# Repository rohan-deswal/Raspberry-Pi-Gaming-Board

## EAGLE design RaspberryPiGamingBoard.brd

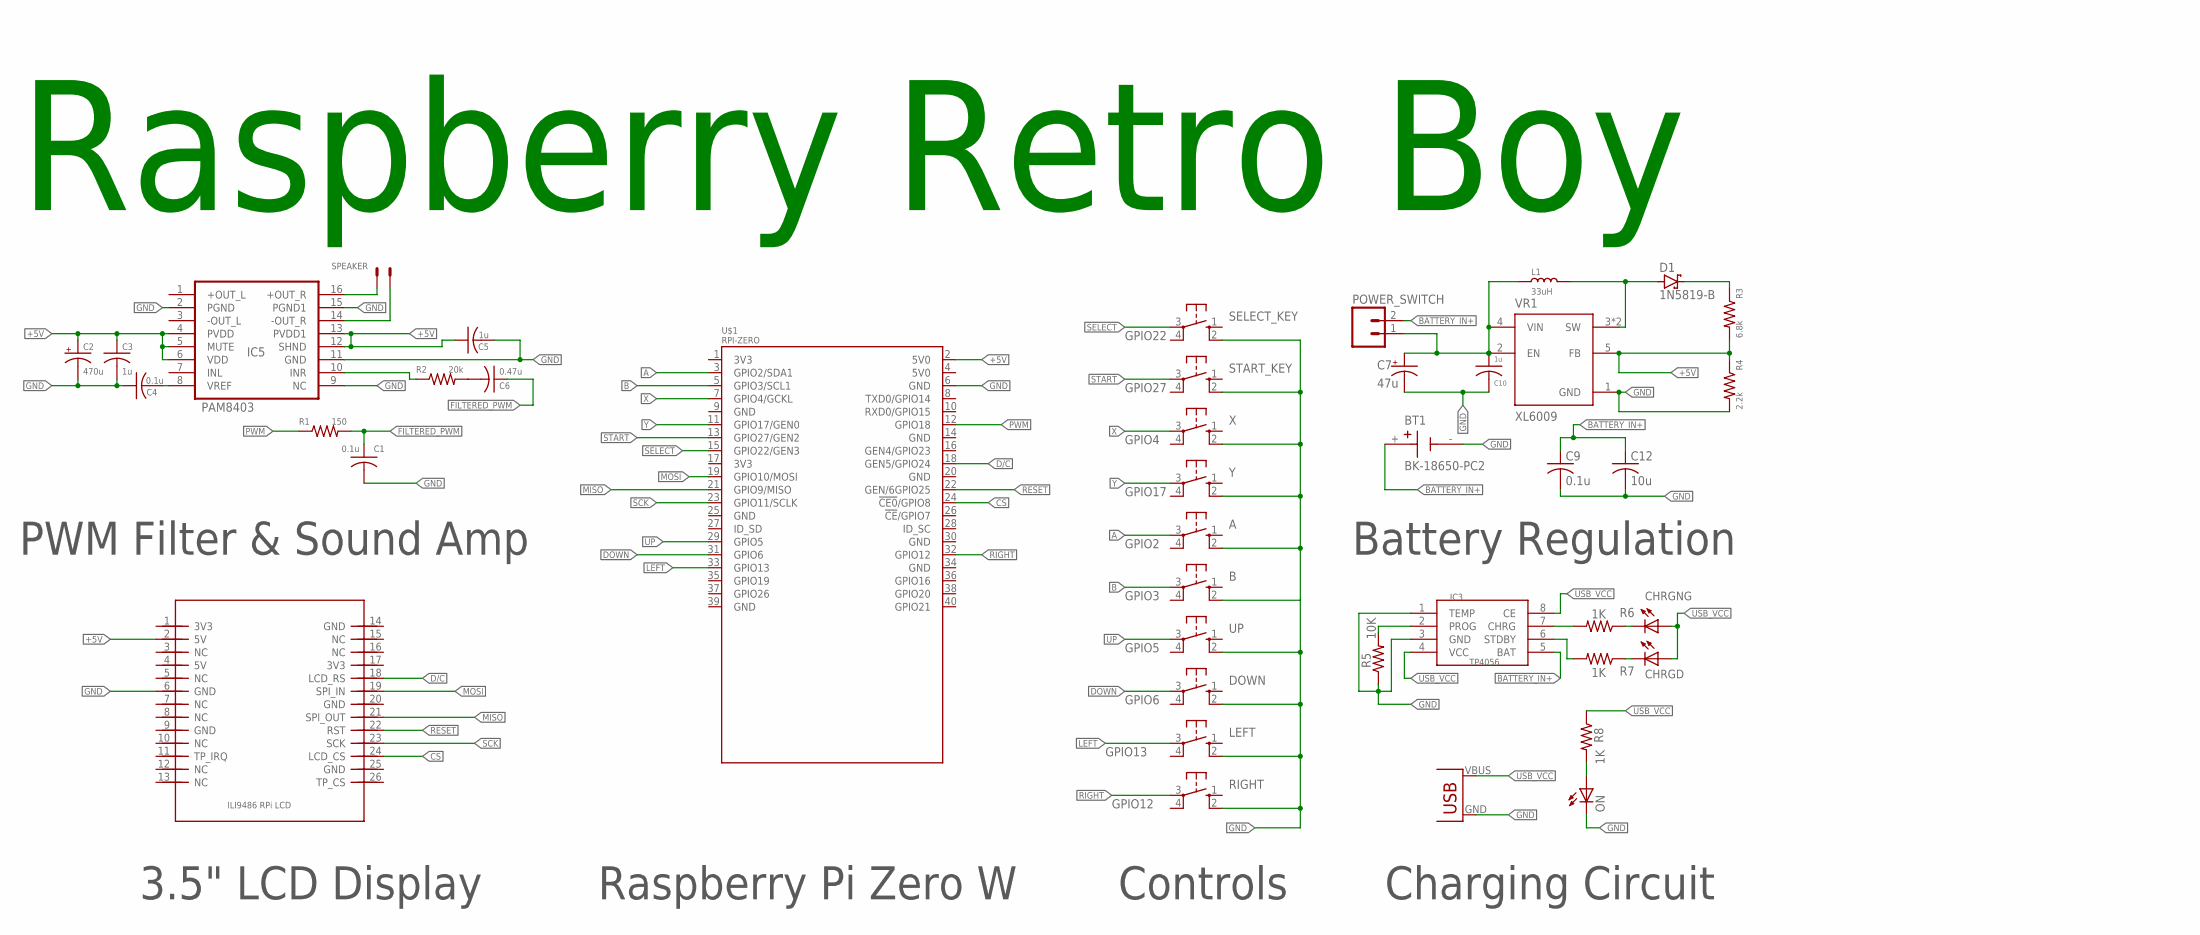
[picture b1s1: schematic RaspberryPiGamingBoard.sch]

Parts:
A: 40-XX; B3F-40XX
B: 40-XX; B3F-40XX
BT1: BK-18650-PC2; BAT_BK-18650-PC2
C1: 0.1u; C0603
C2: 470u; E5-10,5
C3, C5, C10: 1u; C0805
C4, C9: 0.1u; C0805
C6: 0.47u; C0603
C7: 47u; E5-8,5
C12: 10u; C0805
CHRGD: LED3MM
CHRGNG: LED3MM
D1: 1N5819-B; DO41-7.6
DOWN: 40-XX; B3F-40XX
IC3: TP4056; SOP-8
IC5: PAM8403; SOP-16
L1: 33uH; INDUCTOR_INT2-3.5-D6.5XH8.0MM
LEFT: 40-XX; B3F-40XX
ON: LED3MM
POWER_SWITCH: M02; 02P
R1: 150; 0207/10
R2: 20k; 0207/10
R3: 6.8k; 0207/10
R4: 2.2k; 0207/10
R5: 10K; 0207/7
R6, R7, R8: 1K; 0207/7
RIGHT: 40-XX; B3F-40XX
SELECT_KEY: 40-XX; B3F-40XX
SPEAKER: SPEAKER; JST-XH-02-PACKAGE-LONG-PAD
START_KEY: 40-XX; B3F-40XX
U$1: RPI-ZERO; RASP_PI_ZERO_BOARD_FULL
U$2: 3.5INCHRPIDISPLAY; 3.5INCH_RPI_LCD
U$3: USB(POWER)
UP: 40-XX; B3F-40XX
VR1: XL6009; DPAK170P1435X465-6N
X: 40-XX; B3F-40XX
Y: 40-XX; B3F-40XX

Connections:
+5V: C2.+, C3.1, C5.1, IC5.4 (PVDD), IC5.5 (MUTE), IC5.6 (VDD), IC5.12 (SHND), IC5.13 (PVDD1), R3.2, R4.1, U$1.2 (5V0), U$2.2 (5V), VR1.5 (FB)
BATTERY_IN+: BT1.+, C9.1, C12.1, IC3.5 (BAT), POWER_SWITCH.2
FILTERED_PWM: C1.1, C6.1, R1.2
GND: A.2 (S1), B.2 (S1), BT1.-, C1.2, C2.-, C3.2, C4.1, C5.2, C7.-, C9.2, C10.2, C12.2, DOWN.2 (S1), IC3.1 (TEMP), IC3.3 (GND), IC5.2 (PGND), IC5.9 (NC), IC5.11 (GND), IC5.15 (PGND1), LEFT.2 (S1), ON.K (C), R4.2, R5.1, RIGHT.2 (S1), SELECT_KEY.2 (S1), START_KEY.2 (S1), U$1.6 (GND), U$2.6 (GND), U$3.GND, UP.2 (S1), VR1.1 (GND), X.2 (S1), Y.2 (S1)
GPIO2: A.3, U$1.3 (GPIO2/SDA1)
GPIO3: B.3, U$1.5 (GPIO3/SCL1)
GPIO4: U$1.7 (GPIO4/GCKL), X.3
GPIO5: U$1.29 (GPIO5), UP.3
GPIO6: DOWN.3, U$1.31 (GPIO6)
GPIO8: U$1.24 (!CE0!/GPIO8), U$2.24 (LCD_CS)
GPIO9: U$1.21 (GPIO9/MISO), U$2.21 (SPI_OUT)
GPIO10: U$1.19 (GPIO10/MOSI), U$2.19 (SPI_IN)
GPIO11: U$1.23 (GPIO11/SCLK), U$2.23 (SCK)
GPIO12: RIGHT.3, U$1.32 (GPIO12)
GPIO13: LEFT.3, U$1.33 (GPIO13)
GPIO17: U$1.11 (GPIO17/GEN0), Y.3
GPIO18: R1.1, U$1.12 (GPIO18)
GPIO22: SELECT_KEY.3, U$1.15 (GPIO22/GEN3)
GPIO24: U$1.18 (GEN5/GPIO24), U$2.18 (LCD_RS)
GPIO25: U$1.22 (GEN/6GPIO25), U$2.22 (RST)
GPIO27: START_KEY.3, U$1.13 (GPIO27/GEN2)
unnamed: IC5.16 (+OUT_R), SPEAKER.2
unnamed: D1.A, L1.2, VR1.3 (SW), VR1.6 (SW)
unnamed: D1.C, R3.1
unnamed: IC5.14 (-OUT_R), SPEAKER.1
unnamed: IC3.2 (PROG), R5.2
unnamed: C4.2, IC5.8 (VREF)
unnamed: C6.2, R2.2
unnamed: IC5.10 (INR), R2.1
unnamed: CHRGNG.K (C), R6.1
unnamed: CHRGD.K (C), R7.1
unnamed: IC3.7 (CHRG), R6.2
unnamed: IC3.6 (STDBY), R7.2
unnamed: C7.+, C10.1, L1.1, POWER_SWITCH.1, VR1.2 (EN), VR1.4 (VIN)
unnamed: ON.A, R8.2
USB_VCC: CHRGD.A, CHRGNG.A, IC3.4 (VCC), IC3.8 (CE), R8.1, U$3.VBUS (VCC)

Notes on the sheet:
Raspberry Pi Zero W
3.5" LCD Display
Controls
PWM Filter & Sound Amp
Battery Regulation
Charging Circuit
Raspberry Retro Boy

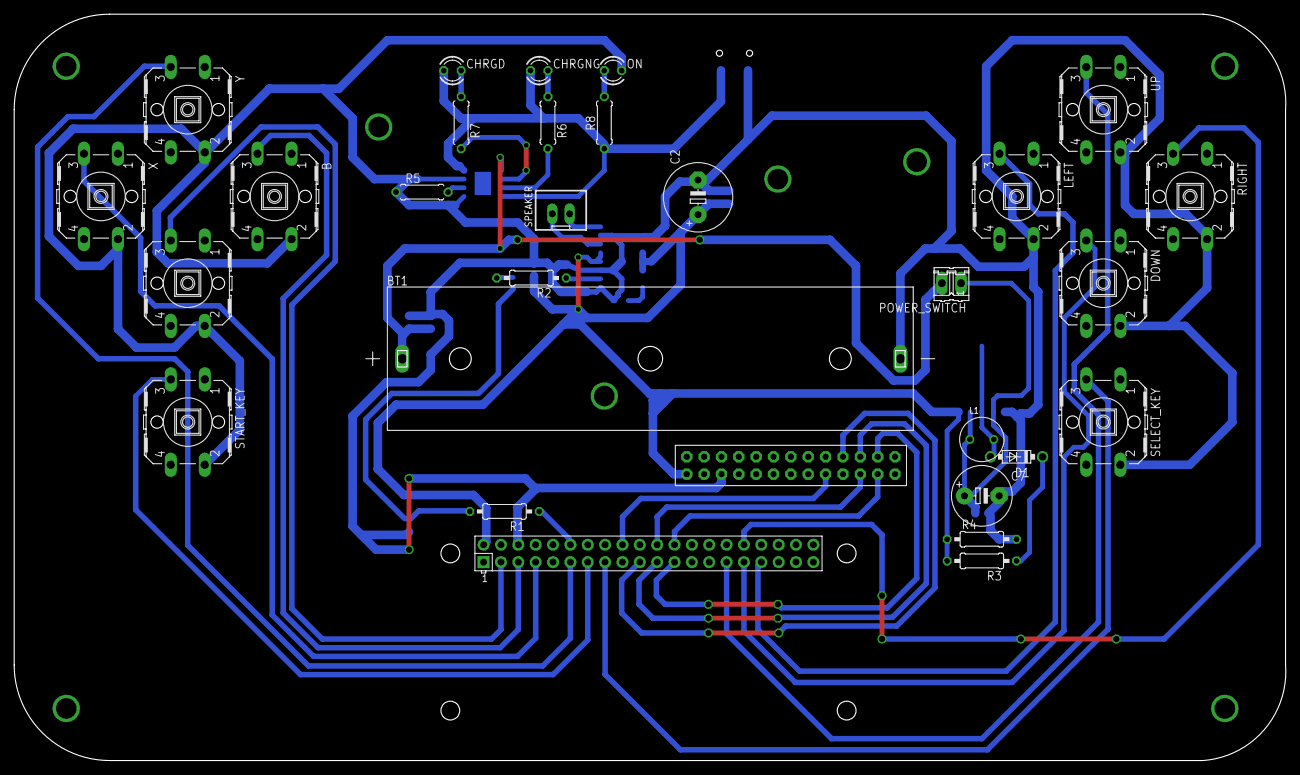
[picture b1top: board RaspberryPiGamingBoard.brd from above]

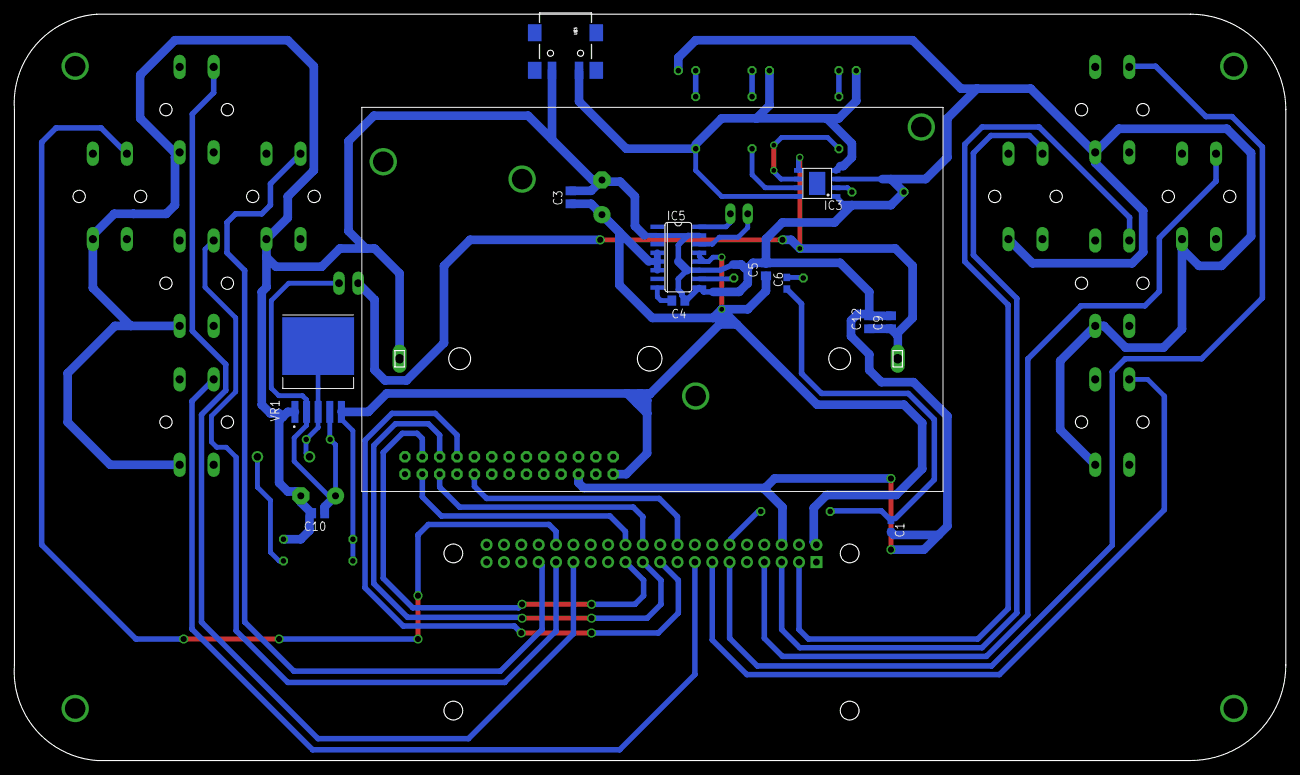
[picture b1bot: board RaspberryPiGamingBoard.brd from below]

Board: 2 copper layers, 186.1 x 109.2 mm, 42 parts (12 on the bottom side), 36 nets.

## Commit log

2022-08-26 v1 of files, schematic and board added
2022-08-30 Batteries and Buttons Rearranged
2023-05-23 Power Supply Setup Reomved
